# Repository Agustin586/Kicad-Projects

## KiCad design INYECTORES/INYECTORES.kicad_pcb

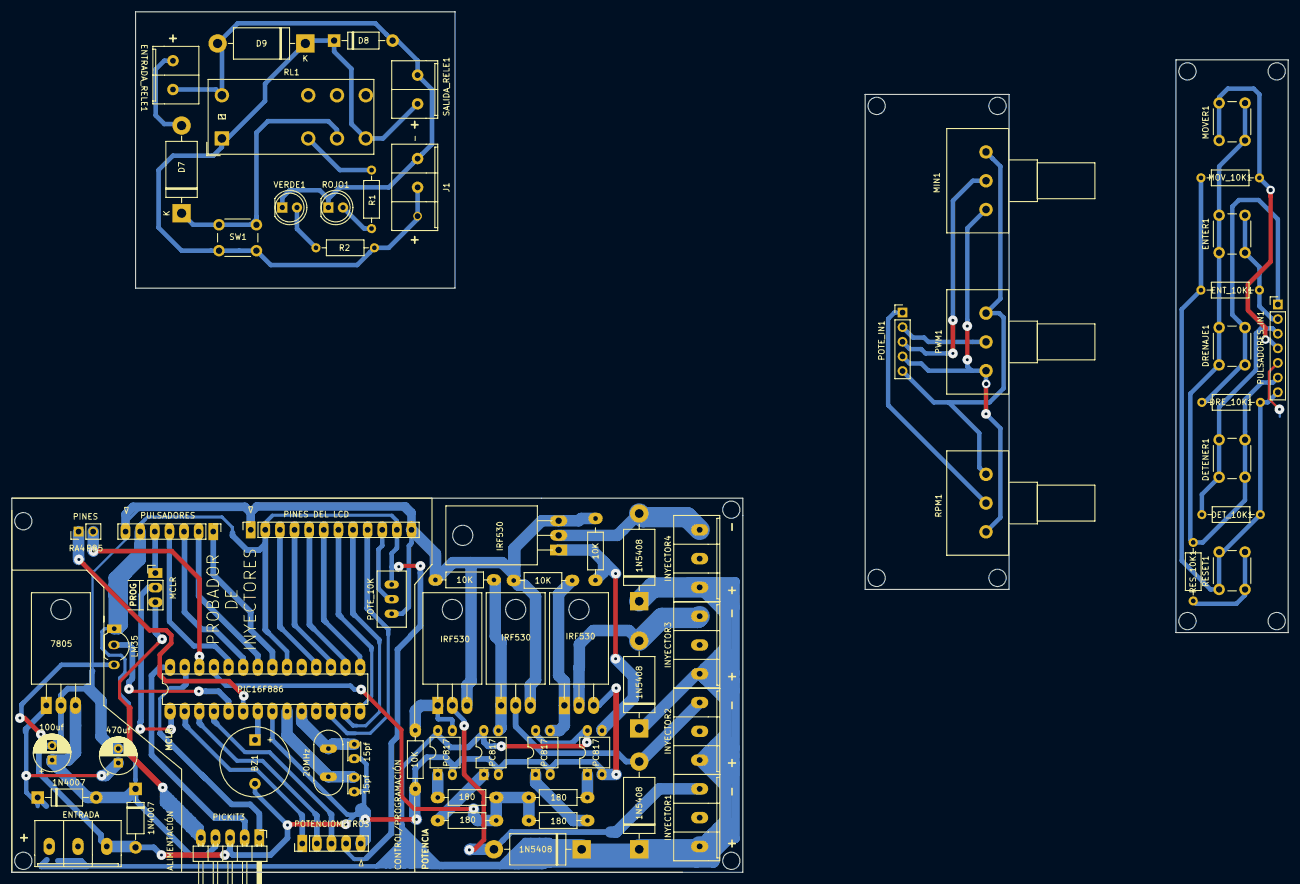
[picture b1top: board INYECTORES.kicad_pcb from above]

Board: 2 copper layers, 221.8 x 149.5 mm, 70 parts (0 on the bottom side), 61 nets.

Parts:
1N4007, 1N4007#2: 1N4007; D_DO-41_SOD81_P10.16mm_Horizontal
1N5408, 1N5408#2, 1N5408#3, 1N5408#4: 1N5404; D_DO-201AD_P15.24mm_Horizontal
10K, 10K#2, 10K#3, 10K#4: 10K; R_Axial_DIN0207_L6.3mm_D2.5mm_P10.16mm_Horizontal
15pf, 15pf#2: 15pf; C_Disc_D3.0mm_W2.0mm_P2.50mm
20MHz: 20MHz; Crystal_HC18-U_Vertical
100uf: 100uf/50v; CP_Radial_D6.3mm_P2.50mm
180, 180#2, 180#3, 180#4: 180; R_Axial_DIN0207_L6.3mm_D2.5mm_P10.16mm_Horizontal
470uf: 470uf/50v; CP_Radial_D6.3mm_P2.50mm
7805: L7805; TO-220-3_Horizontal_TabDown
BZ1: Buzzer; Buzzer_12x9.5RM7.6
D7, D9: 1N5408; D_DO-201AD_P15.24mm_Horizontal
D8: 1N4007; D_DO-41_SOD81_P10.16mm_Horizontal
DETENER1: SW_Push; SW_PUSH_6mm
DET_10K1: 10K; R_Axial_DIN0207_L6.3mm_D2.5mm_P10.16mm_Horizontal
DRENAJE1: SW_Push; SW_PUSH_6mm
DRE_10K1: 10K; R_Axial_DIN0207_L6.3mm_D2.5mm_P10.16mm_Horizontal
ENTER1: SW_Push; SW_PUSH_6mm
ENTRADA: ENTRADA_CIRCUITO; bornera_tornillos_1x03
ENTRADA_RELE1: Screw_Terminal_01x02; bornera_tornillos_1x02
ENT_10K1: 10K; R_Axial_DIN0207_L6.3mm_D2.5mm_P10.16mm_Horizontal
INYECTOR1: INY1; bornera_tornillos_1x03
INYECTOR2: INY2; bornera_tornillos_1x03
INYECTOR3: INY3; bornera_tornillos_1x03
INYECTOR4: INY4; bornera_tornillos_1x03
IRF530, IRF530#2, IRF530#3, IRF530#4: IRF540N; TO-220-3_Horizontal_TabDown
J1: Screw_Terminal_01x03; bornera_tornillos_1x03
LM35: LM35-LP; TO-92L_Inline_Wide
MCLR: Screw_Terminal_01x03; PinHeader_1x03_P2.54mm_Vertical
MIN1: 5K; Potentiometer_Alps_RK163_Single_Horizontal
MOVER1: SW_Push; SW_PUSH_6mm
MOV_10K1: 10K; R_Axial_DIN0207_L6.3mm_D2.5mm_P10.16mm_Horizontal
PC817: PC817_INY3; DIP-4_W7.62mm
PC817#2: PC817_INY1; DIP-4_W7.62mm
PC817#3: PC817_INY2; DIP-4_W7.62mm
PC817#4: PC817_INY4; DIP-4_W7.62mm
PIC16F886: PIC16F886-IP; DIP-28_W7.62mm
PICKIT3: Screw_Terminal_01x05; PinHeader_1x05_P2.54mm_Horizontal
PINES: Screw_Terminal_01x02; PinHeader_1x02_P2.54mm_Vertical
PINES DEL LCD: Screw_Terminal_01x12; PinSocket_1x12_P2.54mm_Vertical
POTENCIOMETROS: Screw_Terminal_01x05; PinHeader_1x05_P2.54mm_Vertical
POTE_10K: 10K; Potentiometer_Bourns_3296W_Vertical
POTE_IN1: Screw_Terminal_01x05; PinHeader_1x05_P2.54mm_Vertical
PULSADORES: Screw_Terminal_01x07; PinHeader_1x07_P2.54mm_Vertical
PULSADORES_IN1: Screw_Terminal_01x07; PinHeader_1x07_P2.54mm_Vertical
PWM1: 5K; Potentiometer_Alps_RK163_Single_Horizontal
R1, R2: 440; R_Axial_DIN0207_L6.3mm_D2.5mm_P10.16mm_Horizontal
RESET1: SW_Push; SW_PUSH_6mm
RES_10K1: 10k; R_Axial_DIN0207_L6.3mm_D2.5mm_P10.16mm_Horizontal
RL1: JW2; Relay_DPDT_Panasonic_JW2
ROJO1: LED; LED_D5.0mm
RPM1: 5K; Potentiometer_Alps_RK163_Single_Horizontal
SALIDA_RELE1: Screw_Terminal_01x02; bornera_tornillos_1x02
SW1: SW_Push; SW_PUSH_6mm
VERDE1: LED; LED_D5.0mm

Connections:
5V: 1N4007.1, 1N4007#2.2, 100uf.1, 7805.3, LM35.1, PIC16F886.20, PICKIT3.4, PINES DEL LCD.2, PINES DEL LCD.11, POTENCIOMETROS.4, POTE_10K.1, PULSADORES.6
12V: 1N4007#2.1, 1N5408.1, 1N5408#2.1, 1N5408#3.1, 1N5408#4.1, 470uf.1, 7805.1, ENTRADA.1, INYECTOR1.1, INYECTOR2.1, INYECTOR3.1, INYECTOR4.1, PC817.4, PC817#2.4, PC817#3.4, PC817#4.4
/CIRCUITO/DETENER: DETENER1.1, DET_10K1.1, PULSADORES_IN1.3
/CIRCUITO/DRENAJE: DRENAJE1.1, DRE_10K1.1, PULSADORES_IN1.1
/CIRCUITO/ENTER: ENTER1.1, ENT_10K1.1, PULSADORES_IN1.2
/CIRCUITO/GND_POTE: MIN1.3, POTE_IN1.5, PWM1.3, RPM1.3
/CIRCUITO/GND_PULS: DET_10K1.2, DRE_10K1.2, ENT_10K1.2, MOV_10K1.2, PULSADORES_IN1.7, RESET1.1
/CIRCUITO/ICSPCLK: PIC16F886.27, PICKIT3.1
/CIRCUITO/ICSPDAT: PIC16F886.28, PICKIT3.2
/CIRCUITO/LCD: PINES DEL LCD.10, POTE_10K.2
/CIRCUITO/LM35: LM35.2, PIC16F886.5
/CIRCUITO/MCLR: PULSADORES_IN1.5, RESET1.2, RES_10K1.1
/CIRCUITO/MIN: MIN1.2, POTE_IN1.3
/CIRCUITO/MOVER: MOVER1.1, MOV_10K1.1, PULSADORES_IN1.4
/CIRCUITO/PWM: POTE_IN1.2, PWM1.2
/CIRCUITO/RA4: PIC16F886.6, PINES.1
/CIRCUITO/RB5: PIC16F886.26, PINES.2
/CIRCUITO/RESET1: MCLR.2, PIC16F886.1
/CIRCUITO/RPM: POTE_IN1.1, RPM1.2
/CIRCUITO/VCC_POTE: MIN1.1, POTE_IN1.4, PWM1.1, RPM1.1
/CIRCUITO/VCC_PULS: DETENER1.2, DRENAJE1.2, ENTER1.2, MOVER1.2, PULSADORES_IN1.6, RES_10K1.2
/FUENTE/GND_RELE: D8.2, D9.2, ENTRADA_RELE1.2, J1.3, RL1.8, ROJO1.1, SALIDA_RELE1.2, VERDE1.1
GND: 1N4007.2, 10K.1, 10K#2.1, 10K#3.1, 10K#4.1, 15pf.1, 15pf#2.1, 100uf.2, 470uf.2, 7805.2, BZ1.2, ENTRADA.3, IRF530.3, IRF530#2.3, IRF530#3.3, IRF530#4.3, LM35.3, PC817.2, PC817#2.2, PC817#3.2, PC817#4.2, PIC16F886.8, PICKIT3.3, PINES DEL LCD.1, PINES DEL LCD.12, POTENCIOMETROS.5, POTE_10K.3, PULSADORES.7
unnamed: BZ1.1, PIC16F886.7
unnamed: 15pf#2.2, 20MHz.1, PIC16F886.10
unnamed: 15pf.2, 20MHz.2, PIC16F886.9
unnamed: 1N5408#4.2, INYECTOR1.3, IRF530#4.2
unnamed: 1N5408#2.2, INYECTOR2.3, IRF530.2
unnamed: 1N5408#3.2, INYECTOR3.3, IRF530#2.2
unnamed: 1N5408.2, INYECTOR4.3, IRF530#3.2
unnamed: D7.1, RL1.3, SW1.1
unnamed: D7.2, ENTRADA_RELE1.1
unnamed: D8.1, D9.1, J1.1, J1.2, R2.1, RL1.1, RL1.4, SALIDA_RELE1.1, SW1.2
unnamed: MCLR.1, PULSADORES.5
unnamed: MCLR.3, PICKIT3.5
unnamed: PIC16F886.18, PINES DEL LCD.3
unnamed: PIC16F886.17, PINES DEL LCD.4
unnamed: PIC16F886.16, PINES DEL LCD.5
unnamed: PIC16F886.15, PINES DEL LCD.6
unnamed: PIC16F886.14, PINES DEL LCD.7
unnamed: PIC16F886.13, PINES DEL LCD.8
unnamed: PIC16F886.12, PINES DEL LCD.9
unnamed: PIC16F886.2, POTENCIOMETROS.1
unnamed: PIC16F886.3, POTENCIOMETROS.2
unnamed: PIC16F886.4, POTENCIOMETROS.3
unnamed: PIC16F886.21, PULSADORES.1
unnamed: PIC16F886.22, PULSADORES.2
unnamed: PIC16F886.23, PULSADORES.3
unnamed: PIC16F886.24, PULSADORES.4
unnamed: 10K#4.2, IRF530#4.1, PC817#2.3
unnamed: 10K#3.2, IRF530.1, PC817#3.3
unnamed: 10K.2, IRF530#2.1, PC817.3
unnamed: 10K#2.2, IRF530#3.1, PC817#4.3
unnamed: R1.1, RL1.2
unnamed: R1.2, ROJO1.2
unnamed: R2.2, VERDE1.2
unnamed: 180#3.1, PC817#2.1
unnamed: 180#4.1, PC817#3.1
unnamed: 180#2.1, PC817.1
unnamed: 180.1, PC817#4.1
OUT: 180.2, 180#2.2, 180#3.2, 180#4.2, PIC16F886.25

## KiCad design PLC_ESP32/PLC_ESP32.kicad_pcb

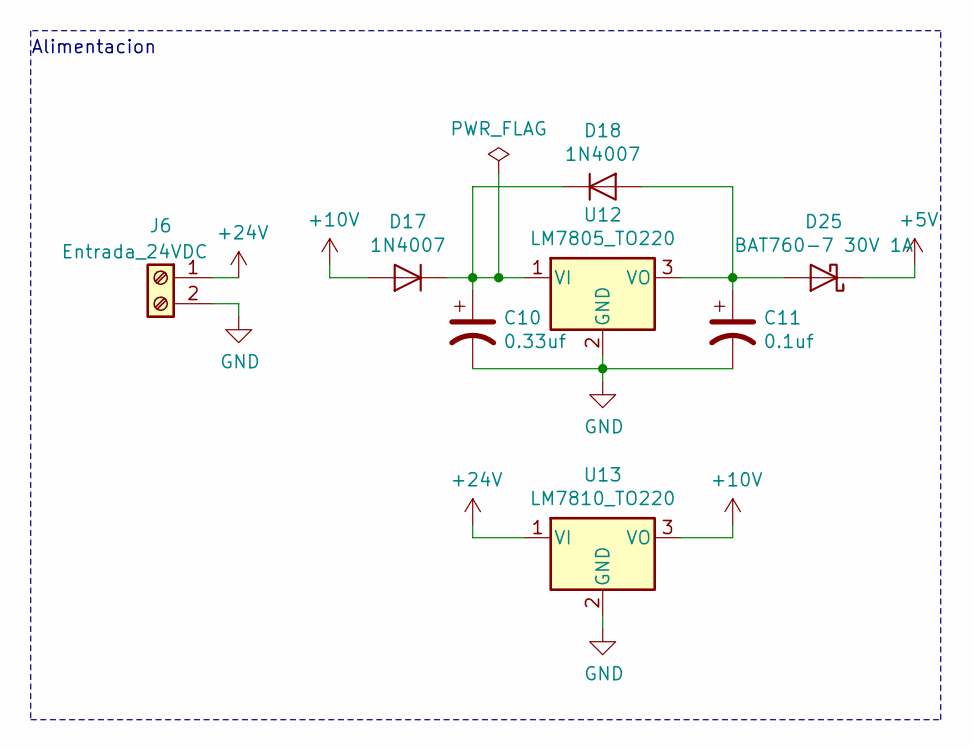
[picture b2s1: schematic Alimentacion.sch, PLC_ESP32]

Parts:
C10: 0.33uf; CP_Radial_D5.0mm_P2.00mm
C11: 0.1uf; CP_Radial_D5.0mm_P2.00mm
D17, D18: 1N4007; D_DO-41_SOD81_P10.16mm_Horizontal
D25: BAT760-7 30V 1A; D_DO-41_SOD81_P10.16mm_Horizontal
J6: Entrada_24VDC; TerminalBlock_Phoenix_PT-1,5-2-5.0-H_1x02_P5.00mm_Horizontal
U12: LM7805_TO220; TO-220-3_Vertical
U13: LM7810_TO220; TO-220-3_Vertical

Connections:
+5V: D25.1 (K); also elsewhere on the board
+10V: D17.2 (A), U13.3 (VO); also elsewhere on the board
+24V: J6.1, U13.1 (VI); also elsewhere on the board
unnamed: C10.1, D17.1 (K), D18.1 (K), U12.1 (VI)
unnamed: C11.1, D18.2 (A), D25.2 (A), U12.3 (VO)

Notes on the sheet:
Alimentacion

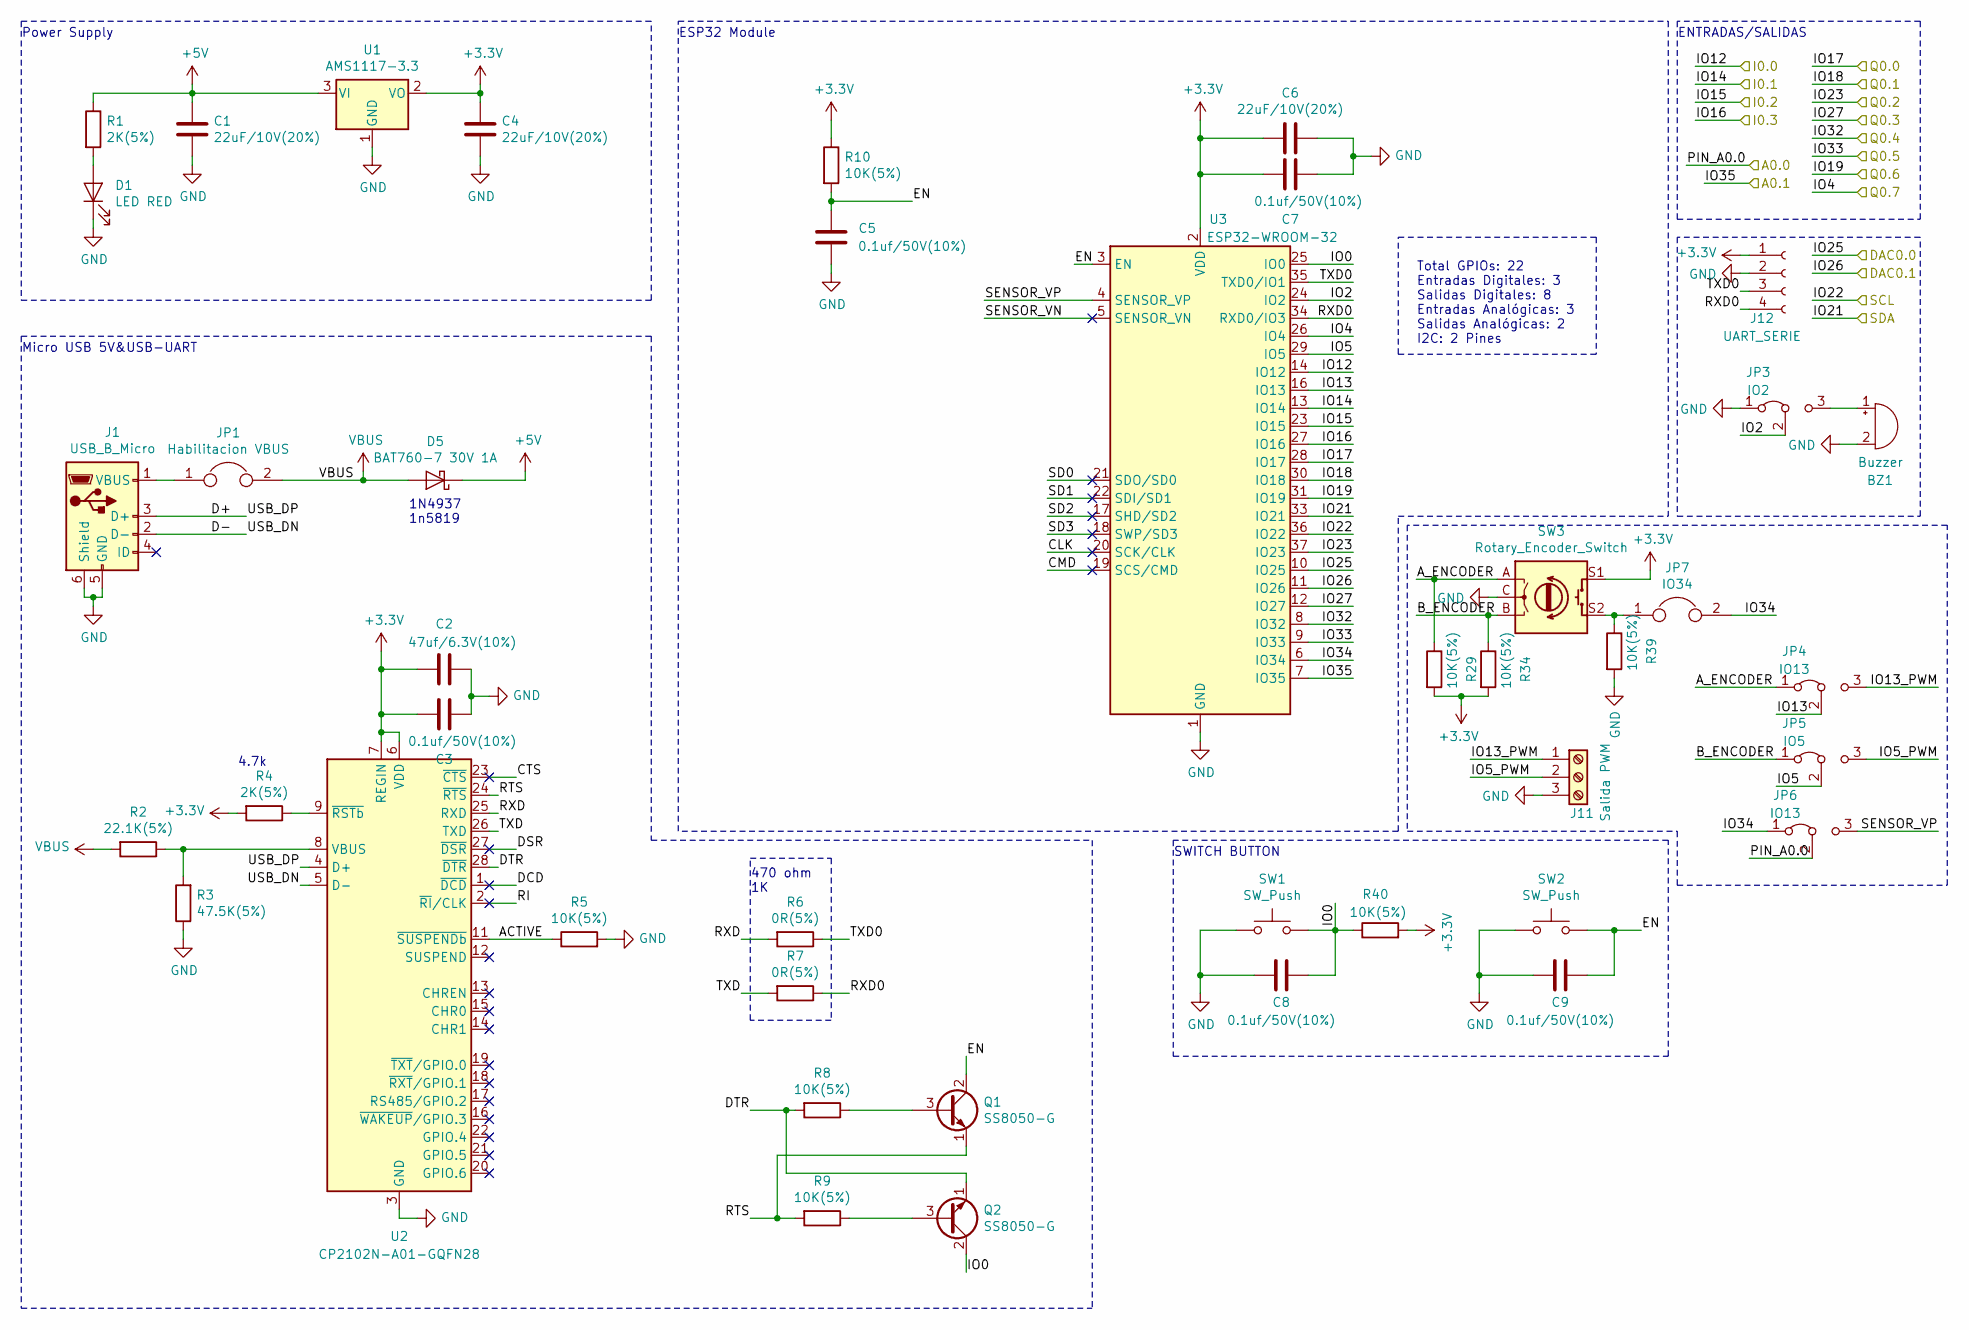
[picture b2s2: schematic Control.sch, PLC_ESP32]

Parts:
BZ1: Buzzer; Buzzer_12x9.5RM7.6
C1, C4, C6: 22uF/10V(20%); C_0805_2012Metric
C2: 47uf/6.3V(10%); C_0805_2012Metric
C3, C5, C7, C8, C9: 0.1uf/50V(10%); C_0805_2012Metric
D1: LED RED; LED_0805_2012Metric
D5: BAT760-7 30V 1A; D_DO-41_SOD81_P10.16mm_Horizontal
J1: USB_B_Micro; Conn_USBmicro-B_ebay-side_TH
J11: Salida PWM; TerminalBlock_Phoenix_PT-1,5-3-5.0-H_1x03_P5.00mm_Horizontal
J12: UART_SERIE; PinSocket_1x04_P2.54mm_Horizontal
JP1: Habilitacion VBUS; PinHeader_1x02_P2.54mm_Vertical
JP3: IO2; PinHeader_1x03_P2.54mm_Vertical
JP4, JP6: IO13; PinHeader_1x03_P2.54mm_Vertical
JP5: IO5; PinHeader_1x03_P2.54mm_Vertical
JP7: IO34; PinHeader_1x02_P2.54mm_Vertical
Q1, Q2: SS8050-G; SOT-23
R1, R4: 2K(5%); R_0805_2012Metric
R2: 22.1K(5%); R_0805_2012Metric
R3: 47.5K(5%); R_0805_2012Metric
R5, R8, R9, R10, R29, R34, R39, R40: 10K(5%); R_0805_2012Metric
R6, R7: 0R(5%); R_0805_2012Metric
SW1, SW2: SW_Push; SW_PUSH_6mm
SW3: Rotary_Encoder_Switch; RotaryEncoder_Alps_EC12E-Switch_Vertical_H20mm
U1: AMS1117-3.3; SOT-223-3_TabPin2
U2: CP2102N-A01-GQFN28; QFN-28-1EP_5x5mm_P0.5mm_EP3.35x3.35mm
U3: ESP32-WROOM-32

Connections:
+5V: C1.1, D5.1 (K), R1.1, U1.3 (VI); also elsewhere on the board
/Control/A0.0: JP6.3 (B), U3.4 (SENSOR_VP); also elsewhere on the board
/Control/A0.1: U3.7 (IO35); also elsewhere on the board
/Control/ACTIVE: R5.1, U2.11 (~SUSPENDb)
/Control/CLK: U3.20 (SCK/CLK)
/Control/CMD: U3.19 (SCS/CMD)
/Control/CTS: U2.23 (~CTS)
/Control/D+: J1.3 (D+), U2.4 (D+)
/Control/D-: J1.2 (D-), U2.5 (D-)
/Control/DAC0.0: U3.10 (IO25); also elsewhere on the board
/Control/DAC0.1: U3.11 (IO26); also elsewhere on the board
/Control/DCD: U2.1 (~DCD)
/Control/DSR: U2.27 (~DSR)
/Control/DTR: Q2.1 (E), R8.2, U2.28 (~DTR)
/Control/EN: C5.1, C9.1, Q1.2 (C), R10.2, SW2.2, U3.3 (EN)
/Control/I0.0: JP5.2 (C), U3.29 (IO5); also elsewhere on the board
/Control/I0.1: U3.23 (IO15); also elsewhere on the board
/Control/I0.2: U3.27 (IO16); also elsewhere on the board
/Control/I0.3: JP6.1 (A), JP7.2, U3.6 (IO34); also elsewhere on the board
/Control/IO0: C8.1, Q2.2 (C), R40.1, SW1.2, U3.25 (IO0)
/Control/IO2: JP3.2 (C), U3.24 (IO2)
/Control/Q0.0: U3.26 (IO4); also elsewhere on the board
/Control/Q0.1: U3.28 (IO17); also elsewhere on the board
/Control/Q0.2: U3.30 (IO18); also elsewhere on the board
/Control/Q0.3: U3.31 (IO19); also elsewhere on the board
/Control/Q0.4: U3.37 (IO23); also elsewhere on the board
/Control/Q0.5: U3.12 (IO27); also elsewhere on the board
/Control/Q0.6: U3.8 (IO32); also elsewhere on the board
/Control/Q0.7: U3.9 (IO33); also elsewhere on the board
/Control/RI: U2.2 (~RI~/CLK)
/Control/RTS: Q1.1 (E), R9.2, U2.24 (~RTS)
/Control/RXD: R6.2, U2.25 (RXD)
/Control/RXD0: J12.4, R7.1, U3.34 (RXD0/IO3)
/Control/SCL: U3.36 (IO22); also elsewhere on the board
/Control/SD0: U3.21 (SDO/SD0)
/Control/SD1: U3.22 (SDI/SD1)
/Control/SD2: U3.17 (SHD/SD2)
/Control/SD3: U3.18 (SWP/SD3)
/Control/SDA: U3.33 (IO21); also elsewhere on the board
/Control/SENSOR_VN: U3.5 (SENSOR_VN)
/Control/TXD: R7.2, U2.26 (TXD)
/Control/TXD0: J12.3, R6.1, U3.35 (TXD0/IO1)
unnamed: BZ1.1 (-), JP3.3 (B)
unnamed: D1.2 (A), R1.2
unnamed 72: JP7.1, R39.1, SW3.S2; also elsewhere on the board
unnamed 73: JP5.1 (A), R34.1, SW3.B; also elsewhere on the board
unnamed 74: JP4.1 (A), R29.1, SW3.A; also elsewhere on the board
unnamed: J1.1 (VBUS), JP1.1
unnamed: J11.1, JP4.3 (B)
unnamed: J11.2, JP5.3 (B)
unnamed: Q1.3 (B), R8.1
unnamed: Q2.3 (B), R9.1
unnamed: R2.1, R3.2, U2.8 (VBUS)
unnamed: R4.1, U2.9 (~RSTb)
VBUS: D5.2 (A), JP1.2, R2.2

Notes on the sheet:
Power Supply
Micro USB 5V&USB-UART
ESP32 Module
SWITCH BUTTON
Total GPIOs: 22 Entradas Digitales: 3 Salidas Digitales: 8 Entradas Analógicas: 3 Salidas Analógicas: 2 I2C: 2 Pines
ENTRADAS/SALIDAS
1N4937 1n5819
470 ohm 1K
4.7k

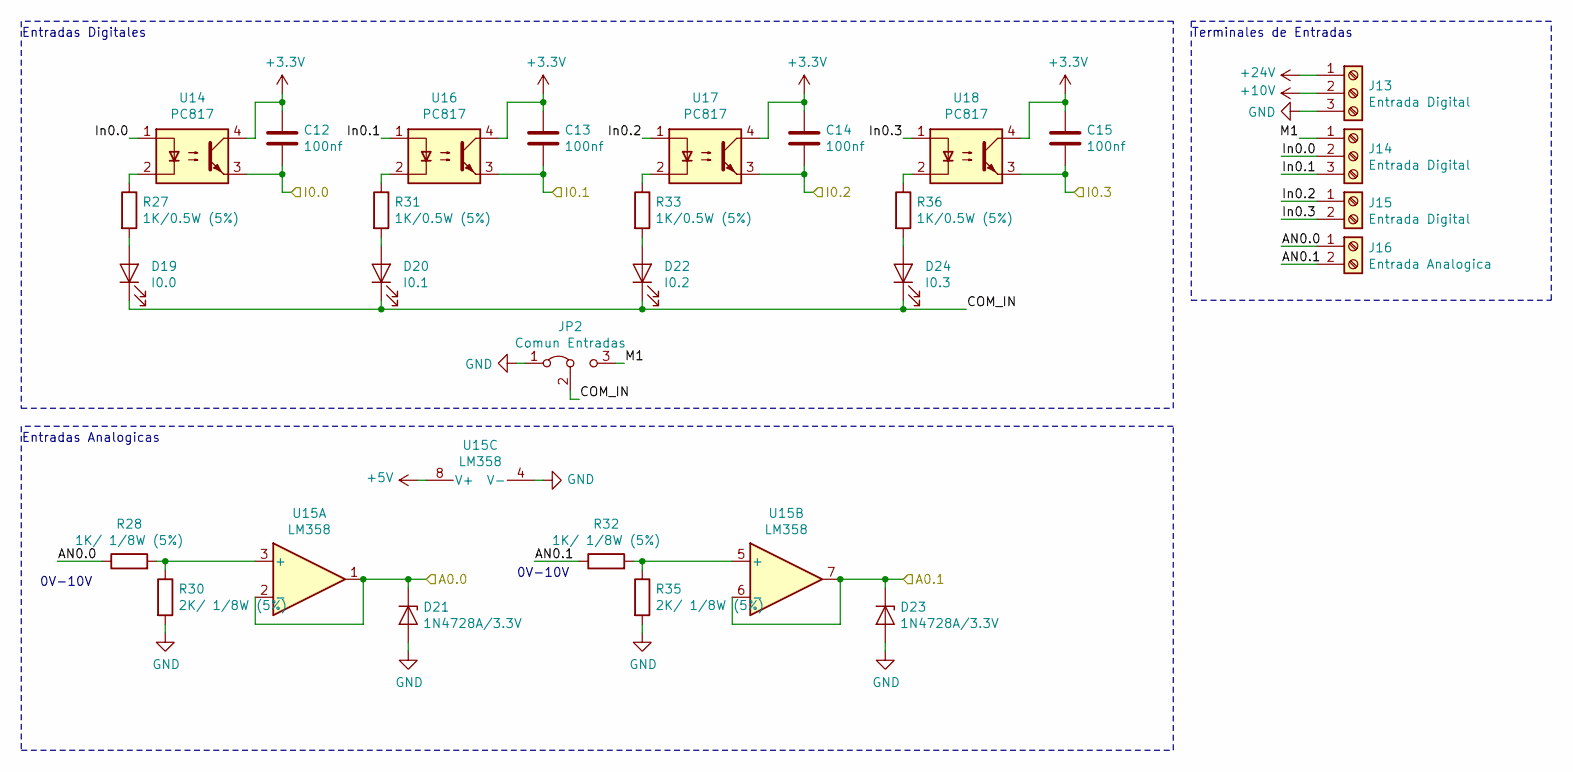
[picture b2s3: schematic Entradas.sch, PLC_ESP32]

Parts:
C12, C13, C14, C15: 100nf; C_Disc_D5.0mm_W2.5mm_P2.50mm
D19: I0.0; LED_0805_2012Metric
D20: I0.1; LED_0805_2012Metric
D21, D23: 1N4728A/3.3V; D_DO-41_SOD81_P10.16mm_Horizontal
D22: I0.2; LED_0805_2012Metric
D24: I0.3; LED_0805_2012Metric
J13, J14: Entrada Digital; TerminalBlock_Phoenix_PT-1,5-3-5.0-H_1x03_P5.00mm_Horizontal
J15: Entrada Digital; TerminalBlock_Phoenix_PT-1,5-2-5.0-H_1x02_P5.00mm_Horizontal
J16: Entrada Analogica; TerminalBlock_Phoenix_PT-1,5-2-5.0-H_1x02_P5.00mm_Horizontal
JP2: Comun Entradas; PinHeader_1x03_P2.54mm_Vertical
R27, R31, R33, R36: 1K/0.5W (5%); R_Axial_DIN0207_L6.3mm_D2.5mm_P10.16mm_Horizontal
R28, R32: 1K/ 1/8W (5%); R_0805_2012Metric
R30, R35: 2K/ 1/8W (5%); R_0805_2012Metric
U14, U16, U17, U18: PC817; DIP-4_W7.62mm_LongPads
U15: LM358; SOIC-8_3.9x4.9mm_P1.27mm

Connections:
+5V: U15.8 (V+); also elsewhere on the board
+10V: J13.2; also elsewhere on the board
+24V: J13.1; also elsewhere on the board
/Control/A0.0: D21.1 (K), U15.1, U15.2 (-); also elsewhere on the board
/Control/A0.1: D23.1 (K), U15.6 (-), U15.7; also elsewhere on the board
/Control/I0.0: C12.2, U14.3; also elsewhere on the board
/Control/I0.1: C13.2, U16.3; also elsewhere on the board
/Control/I0.2: C14.2, U17.3; also elsewhere on the board
/Control/I0.3: C15.2, U18.3; also elsewhere on the board
/Entradas/AN0.0: J16.1, R28.1
/Entradas/AN0.1: J16.2, R32.1
/Entradas/COM_IN: D19.1 (K), D20.1 (K), D22.1 (K), D24.1 (K), JP2.2 (C)
/Entradas/In0.0: J14.2, U14.1
/Entradas/In0.1: J14.3, U16.1
/Entradas/In0.2: J15.1, U17.1
/Entradas/In0.3: J15.2, U18.1
/Entradas/M1: J14.1, JP2.3 (B)
unnamed: D19.2 (A), R27.2
unnamed: D20.2 (A), R31.2
unnamed: D22.2 (A), R33.2
unnamed: D24.2 (A), R36.2
unnamed: R27.1, U14.2
unnamed: R28.2, R30.1, U15.3 (+)
unnamed: R31.1, U16.2
unnamed: R32.2, R35.1, U15.5 (+)
unnamed: R33.1, U17.2
unnamed: R36.1, U18.2

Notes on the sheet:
Entradas Digitales
Entradas Analogicas
Terminales de Entradas
0V-10V

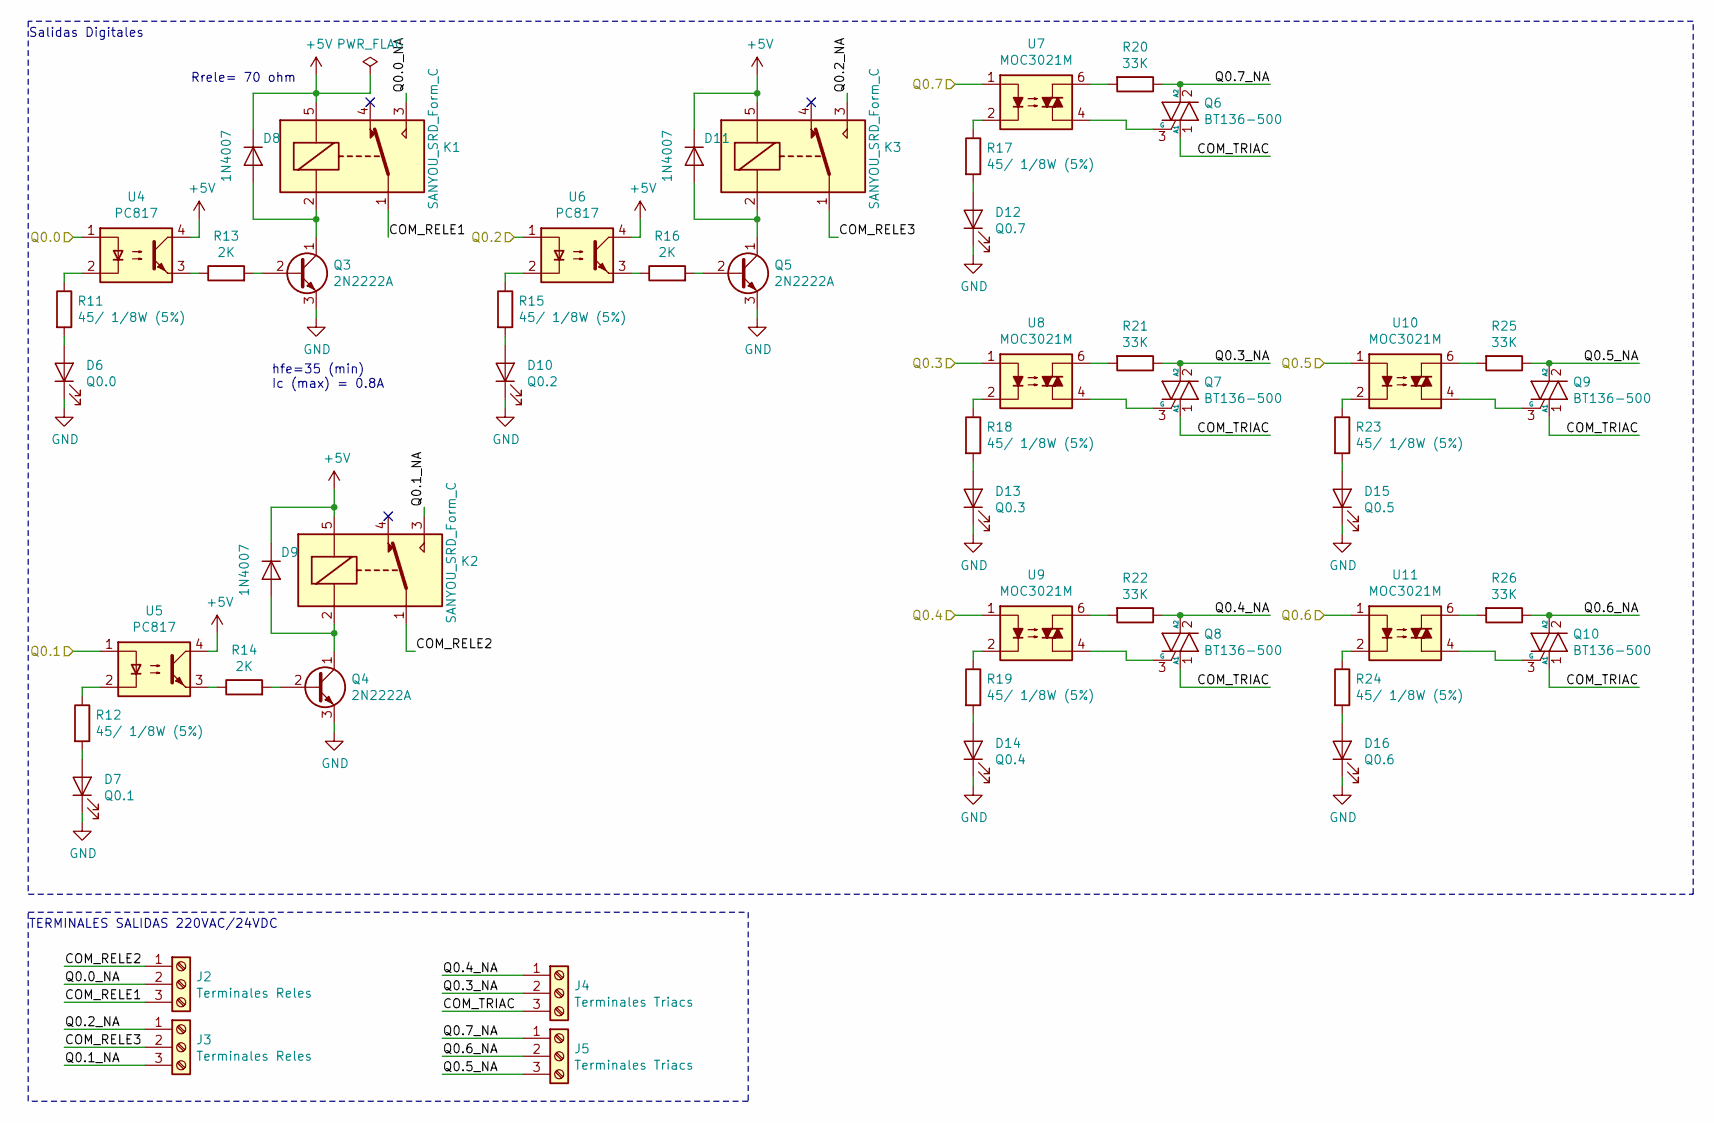
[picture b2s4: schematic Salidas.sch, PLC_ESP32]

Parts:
D6: Q0.0; LED_0805_2012Metric
D7: Q0.1; LED_0805_2012Metric
D8, D9, D11: 1N4007; D_DO-41_SOD81_P10.16mm_Horizontal
D10: Q0.2; LED_0805_2012Metric
D12: Q0.7; LED_0805_2012Metric
D13: Q0.3; LED_0805_2012Metric
D14: Q0.4; LED_0805_2012Metric
D15: Q0.5; LED_0805_2012Metric
D16: Q0.6; LED_0805_2012Metric
J2, J3: Terminales Reles; TerminalBlock_Phoenix_PT-1,5-3-5.0-H_1x03_P5.00mm_Horizontal
J4, J5: Terminales Triacs; TerminalBlock_Phoenix_PT-1,5-3-5.0-H_1x03_P5.00mm_Horizontal
K1, K2, K3: SANYOU_SRD_Form_C; Relay_SPDT_SANYOU_SRD_Series_Form_C
Q3, Q4, Q5: 2N2222A; TO-92_Inline
Q6, Q7, Q8, Q9, Q10: BT136-500; TO-220-3_Vertical
R11, R12, R15, R17, R18, R19, R23, R24: 45/ 1/8W (5%); R_0805_2012Metric
R13, R14, R16: 2K; R_0805_2012Metric
R20, R21, R22, R25, R26: 33K; R_Axial_DIN0207_L6.3mm_D2.5mm_P10.16mm_Horizontal
U4, U5, U6: PC817; DIP-4_W7.62mm_LongPads
U7, U8, U9, U10, U11: MOC3021M; DIP-6_W7.62mm_LongPads

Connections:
+5V: D8.1 (K), D9.1 (K), D11.1 (K), K1.5, K2.5, K3.5, U4.4, U5.4, U6.4; also elsewhere on the board
/Control/Q0.0: U4.1; also elsewhere on the board
/Control/Q0.1: U5.1; also elsewhere on the board
/Control/Q0.2: U6.1; also elsewhere on the board
/Control/Q0.3: U8.1; also elsewhere on the board
/Control/Q0.4: U9.1; also elsewhere on the board
/Control/Q0.5: U10.1; also elsewhere on the board
/Control/Q0.6: U11.1; also elsewhere on the board
/Control/Q0.7: U7.1; also elsewhere on the board
/Salidas/COM_RELE1: J2.3, K1.1
/Salidas/COM_RELE2: J2.1, K2.1
/Salidas/COM_RELE3: J3.2, K3.1
/Salidas/COM_TRIAC: J4.3, Q6.1 (A1), Q7.1 (A1), Q8.1 (A1), Q9.1 (A1), Q10.1 (A1)
/Salidas/Q0.0_NA: J2.2, K1.3
/Salidas/Q0.1_NA: J3.3, K2.3
/Salidas/Q0.2_NA: J3.1, K3.3
/Salidas/Q0.3_NA: J4.2, Q7.2 (A2), R21.1
/Salidas/Q0.4_NA: J4.1, Q8.2 (A2), R22.1
/Salidas/Q0.5_NA: J5.3, Q9.2 (A2), R25.1
/Salidas/Q0.6_NA: J5.2, Q10.2 (A2), R26.1
/Salidas/Q0.7_NA: J5.1, Q6.2 (A2), R20.1
unnamed: D6.2 (A), R11.2
unnamed: D7.2 (A), R12.2
unnamed: D10.2 (A), R15.2
unnamed: D12.2 (A), R17.2
unnamed: D13.2 (A), R18.2
unnamed: D14.2 (A), R19.2
unnamed: D15.2 (A), R23.2
unnamed: D16.2 (A), R24.2
unnamed: Q3.2 (B), R13.2
unnamed: Q4.2 (B), R14.2
unnamed: Q5.2 (B), R16.2
unnamed: Q6.3 (G), U7.4
unnamed: Q7.3 (G), U8.4
unnamed: Q8.3 (G), U9.4
unnamed: Q9.3 (G), U10.4
unnamed: Q10.3 (G), U11.4
unnamed: R11.1, U4.2
unnamed: R12.1, U5.2
unnamed: R13.1, U4.3
unnamed: R14.1, U5.3
unnamed: R15.1, U6.2
unnamed: R16.1, U6.3
unnamed: R17.1, U7.2
unnamed: R18.1, U8.2
unnamed: R19.1, U9.2
unnamed: R20.2, U7.6
unnamed: R21.2, U8.6
unnamed: R22.2, U9.6
unnamed: R23.1, U10.2
unnamed: R24.1, U11.2
unnamed: R25.2, U10.6
unnamed: R26.2, U11.6

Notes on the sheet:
TERMINALES SALIDAS 220VAC/24VDC
Salidas Digitales
hfe=35 (min) Ic (max) = 0.8A
Rrele= 70 ohm

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
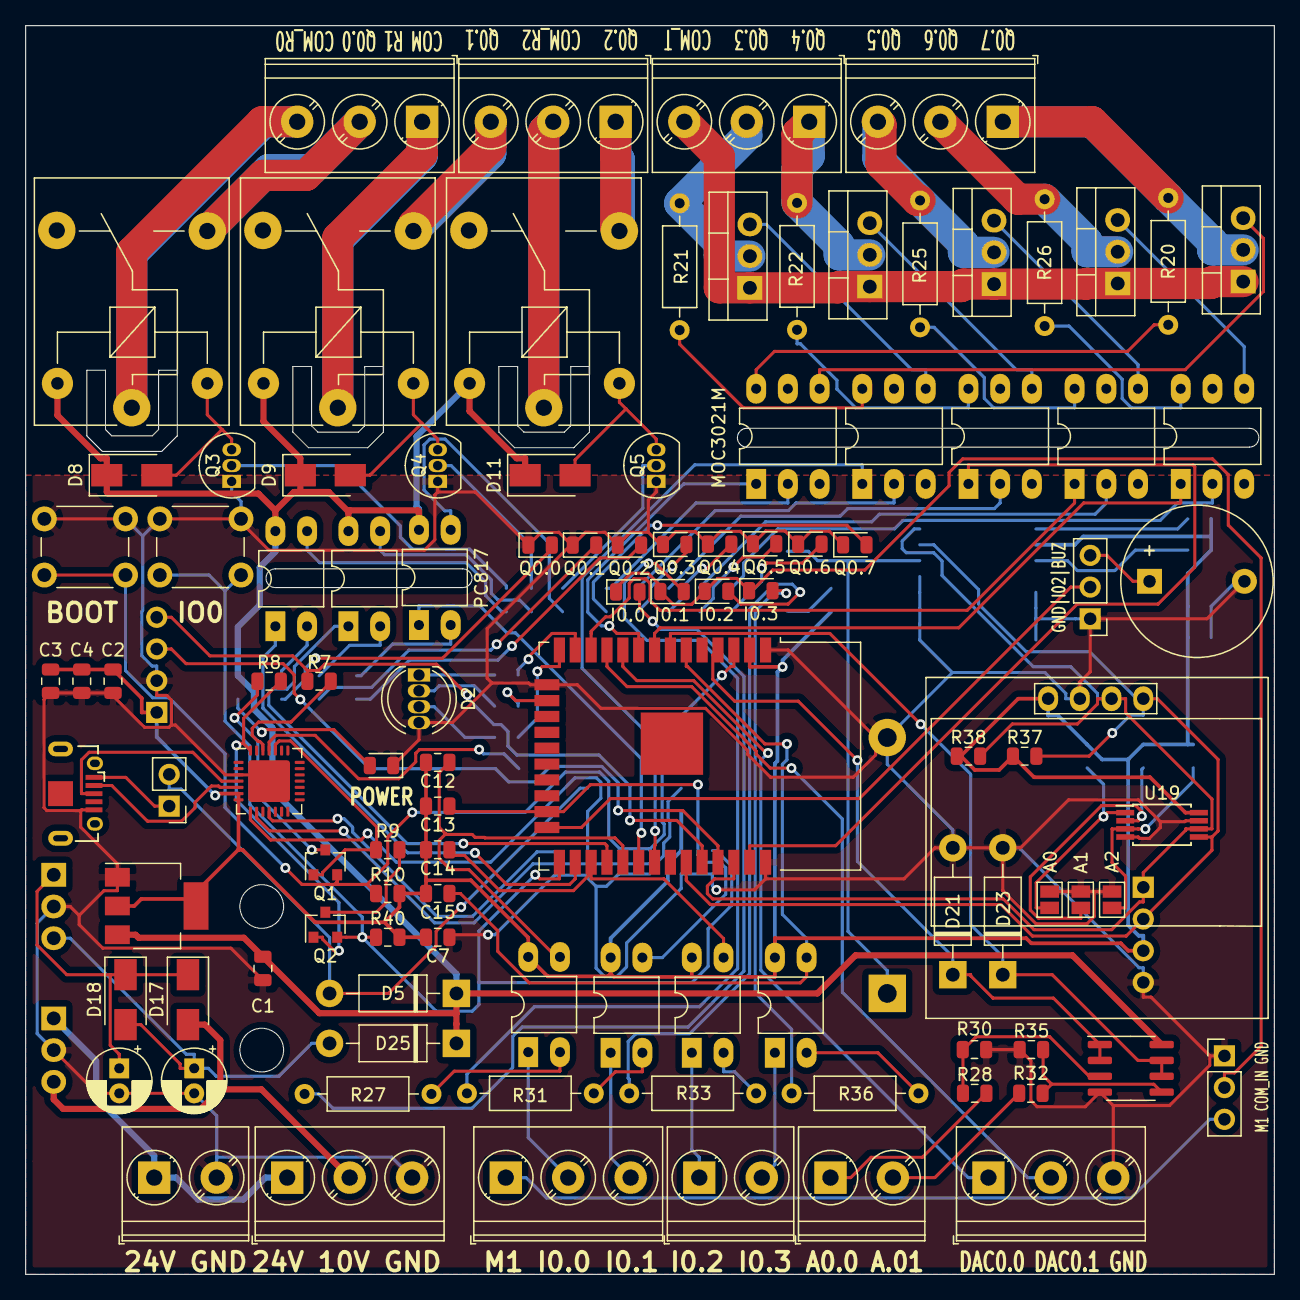
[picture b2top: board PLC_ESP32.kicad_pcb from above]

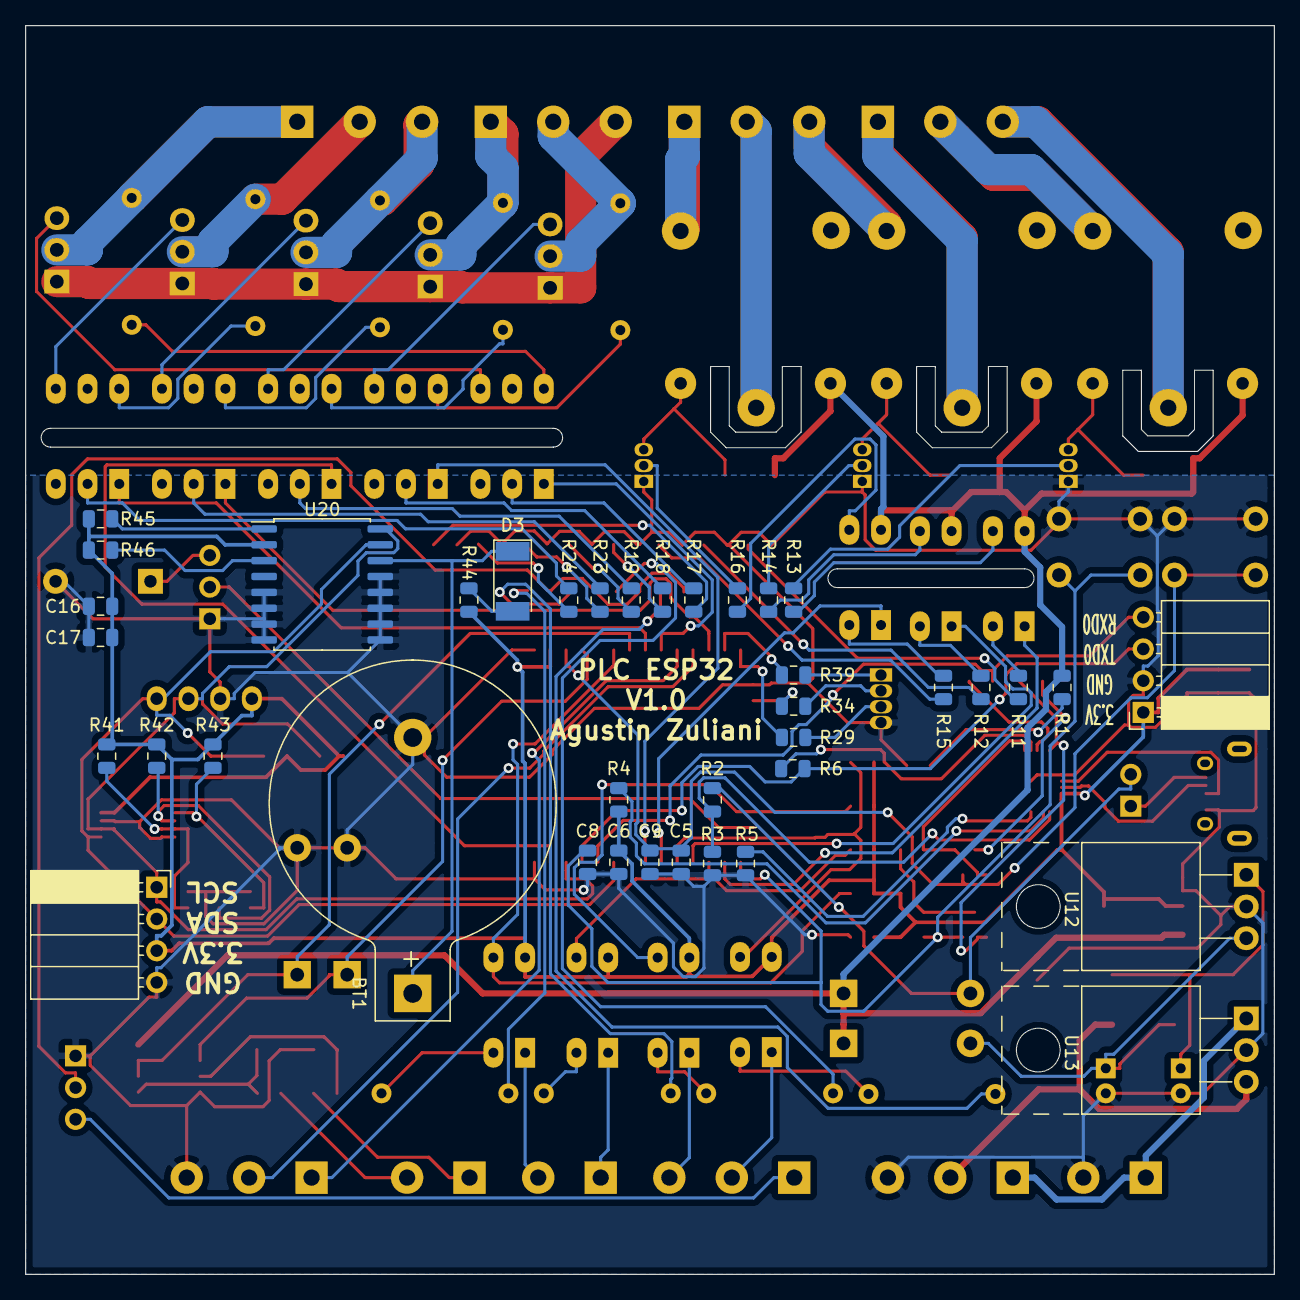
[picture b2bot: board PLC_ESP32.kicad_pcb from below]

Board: 2 copper layers, 100.0 x 100.0 mm, 144 parts (39 on the bottom side), 123 nets.

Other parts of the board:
A0, A1, A2: Jumper; SolderJumper-2_P1.3mm_Open_Pad1.0x1.5mm
BT1: Battery_Cell; BatteryHolder_Keystone_103_1x20mm
C16, C17: 0.1uf; C_0805_2012Metric
D2: LED_RGBC; LED_D5.0mm-4_RGB
D3: 1N4148; D_MELF
J7: PANTALLA LCD I2C; PinSocket_1x04_P2.54mm_Horizontal
J9: PANTALLA OLED; 128x64OLED
J10: Salidas Analogicas; TerminalBlock_Phoenix_PT-1,5-3-5.0-H_1x03_P5.00mm_Horizontal
R37, R38: 2K2 (5%); R_0805_2012Metric
R41, R42, R43, R45, R46: 4K7 1/8W 5%; R_0805_2012Metric
R44: 200 1/8W 5%; R_0805_2012Metric
U19: AT24CS32-XHM; TSSOP-8_4.4x3mm_P0.65mm
U20: DS3231M; SOIC-16W_7.5x10.3mm_P1.27mm

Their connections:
/Control/DAC0.0: J10.1; also elsewhere on the board
/Control/DAC0.1: J10.2; also elsewhere on the board
/Control/SCL: J7.1, J9.3, R38.2, U19.6, U20.16; also elsewhere on the board
/Control/SDA: J7.2, J9.4, R37.2, U19.5, U20.15; also elsewhere on the board
unnamed: A0.2, R43.2, U19.1
unnamed: A1.2, R42.2, U19.2
unnamed: A2.2, R41.2, U19.3
unnamed: BT1.1, D3.1, U20.14
unnamed 72: D2.1; also elsewhere on the board
unnamed 73: D2.2; also elsewhere on the board
unnamed 74: D2.3; also elsewhere on the board
unnamed: D3.2, R44.1
unnamed: R45.2, U20.1
unnamed: R46.2, U20.3
